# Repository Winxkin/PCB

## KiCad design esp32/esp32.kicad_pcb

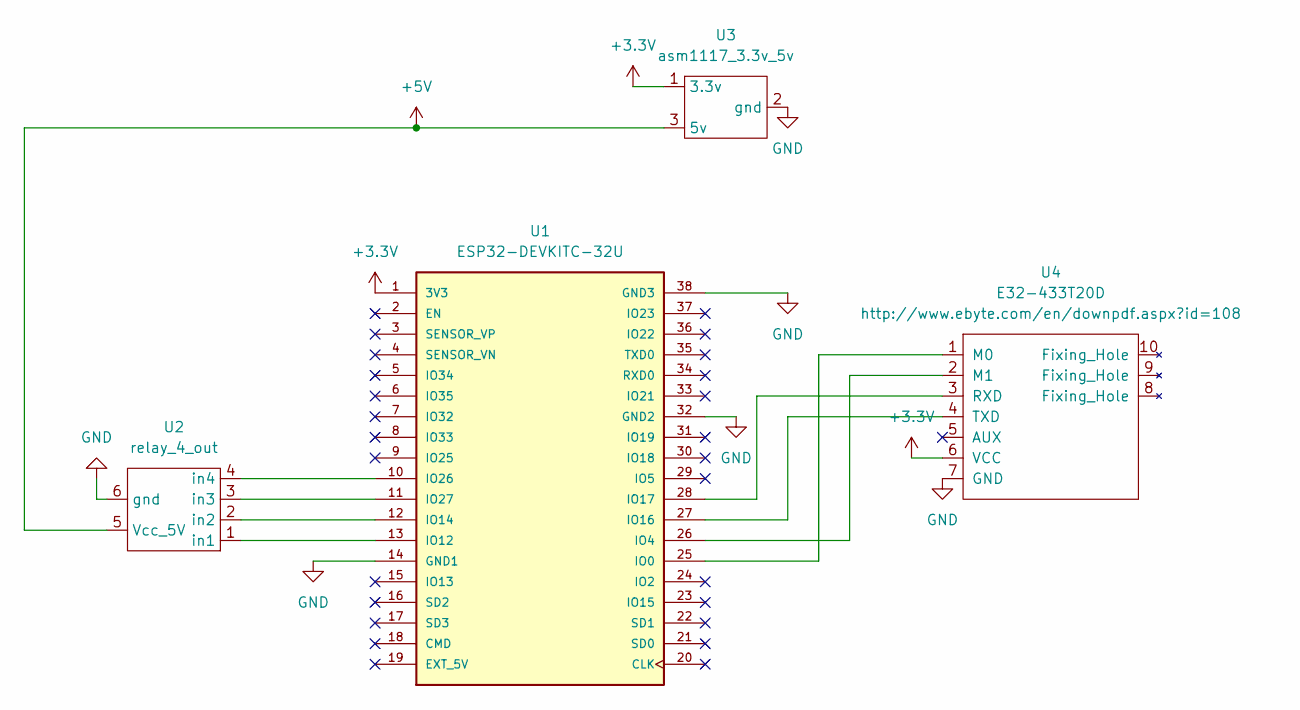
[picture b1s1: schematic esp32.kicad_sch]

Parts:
U1: ESP32-DEVKITC-32U; MODULE_ESP32-DEVKITC-AI-Thinker; PARTREV N/A
U2: relay_4_out
U3: asm1117_3.3v_5v; asm1117_3.3V_5V
U4: E32-433T20D; E32-xxxT20D

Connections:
+3.3V: U1.1 (3V3), U3.1 (3.3v), U4.6 (VCC)
+5V: U2.5 (Vcc_5V), U3.3 (5v)
GND: U1.14 (GND1), U1.32 (GND2), U1.38 (GND3), U2.6 (gnd), U3.2 (gnd), U4.7 (GND)
unnamed: U1.10 (IO26), U2.4 (in4)
unnamed: U1.11 (IO27), U2.3 (in3)
unnamed: U1.12 (IO14), U2.2 (in2)
unnamed: U1.13 (IO12), U2.1 (in1)
unnamed: U1.25 (IO0), U4.1 (M0)
unnamed: U1.26 (IO4), U4.2 (M1)
unnamed: U1.27 (IO16), U4.4 (TXD)
unnamed: U1.28 (IO17), U4.3 (RXD)

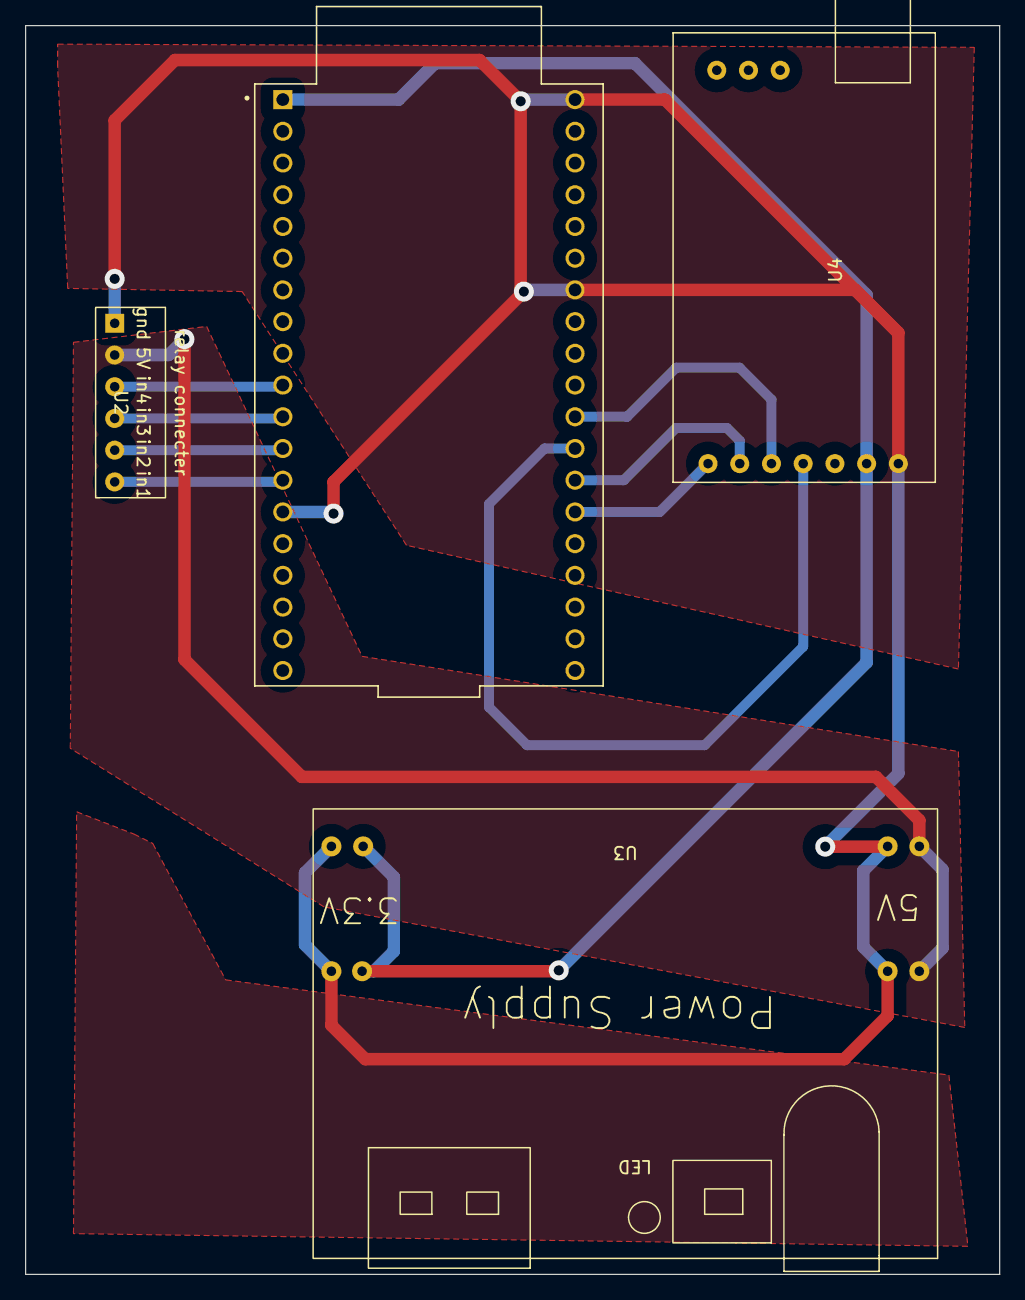
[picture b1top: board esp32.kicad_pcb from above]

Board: 2 copper layers, 78.0 x 100.0 mm, 4 parts (0 on the bottom side), 11 nets.

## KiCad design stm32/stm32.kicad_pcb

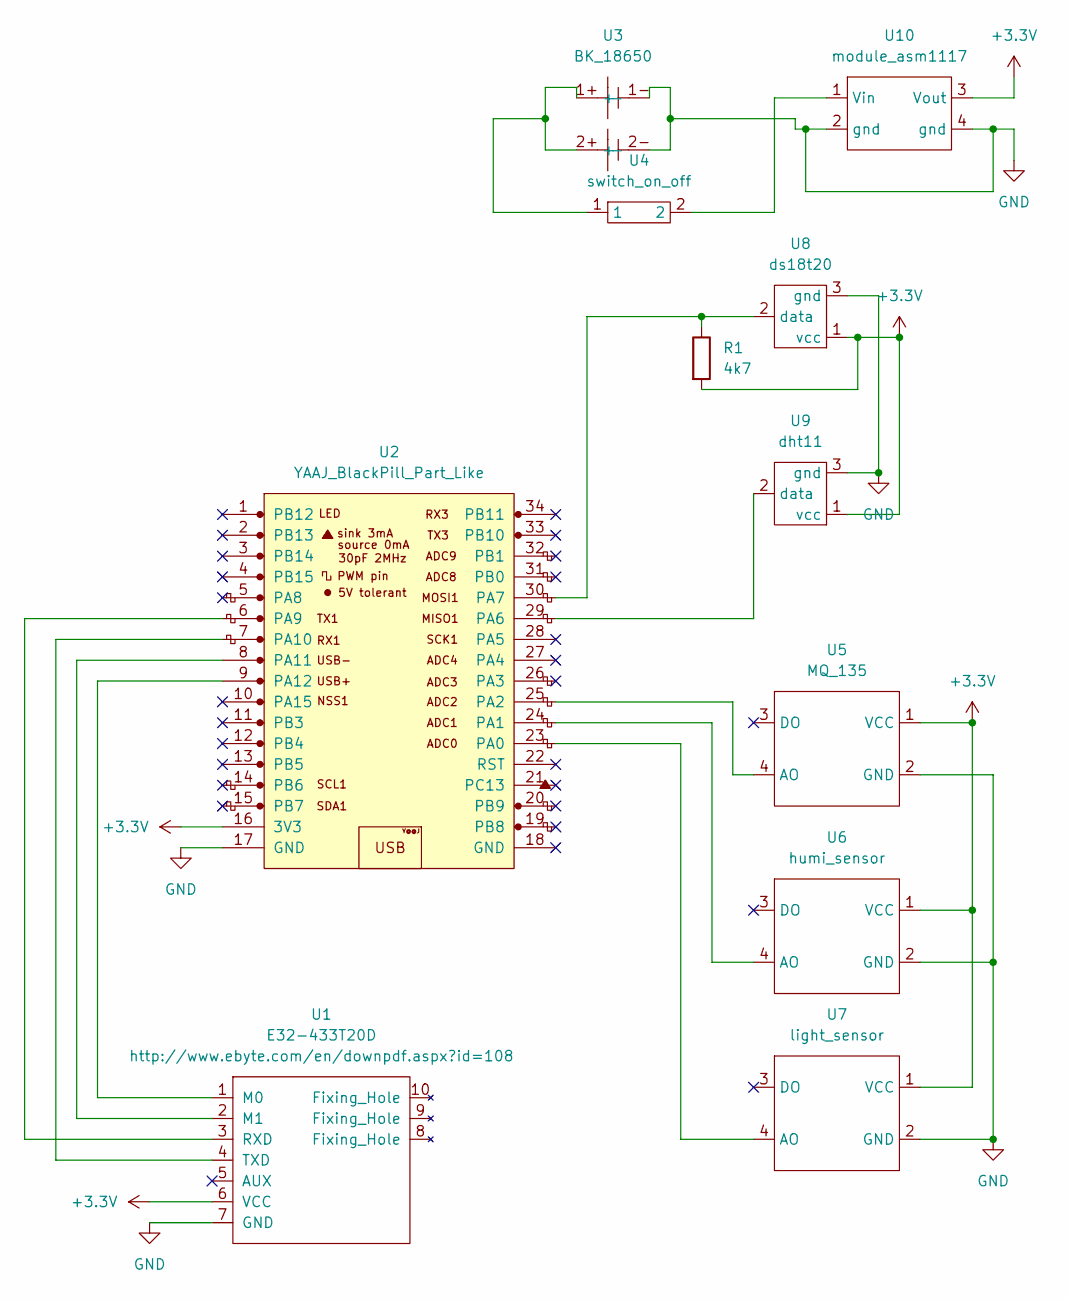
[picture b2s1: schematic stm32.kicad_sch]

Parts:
R1: 4k7; R_Axial_DIN0204_L3.6mm_D1.6mm_P2.54mm_Vertical
U1: E32-433T20D; E32-xxxT20D
U2: YAAJ_BlackPill_Part_Like; YAAJ_BlackPill_1
U3: BK_18650; BAT_BK-18650-PC4
U4: switch_on_off
U5: MQ_135
U6: humi_sensor
U7: light_sensor
U8: ds18t20; dt18s20
U9: dht11; dt18s20
U10: module_asm1117

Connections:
+3.3V: R1.2, U1.6 (VCC), U2.16 (3V3), U5.1 (VCC), U6.1 (VCC), U7.1 (VCC), U8.1 (vcc), U9.1 (vcc), U10.3 (Vout)
GND: U1.7 (GND), U2.17 (GND), U3.1- (-), U3.2- (-), U5.2 (GND), U6.2 (GND), U7.2 (GND), U8.3 (gnd), U9.3 (gnd), U10.2 (gnd), U10.4 (gnd)
unnamed: R1.1, U2.30 (PA7), U8.2 (data)
unnamed: U1.1 (M0), U2.9 (PA12)
unnamed: U1.2 (M1), U2.8 (PA11)
unnamed: U1.3 (RXD), U2.6 (PA9)
unnamed: U1.4 (TXD), U2.7 (PA10)
unnamed: U2.23 (PA0), U7.4 (AO)
unnamed: U2.24 (PA1), U6.4 (AO)
unnamed: U2.25 (PA2), U5.4 (AO)
unnamed: U2.29 (PA6), U9.2 (data)
unnamed: U3.1+ (+), U3.2+ (+), U4.1
unnamed: U4.2, U10.1 (Vin)

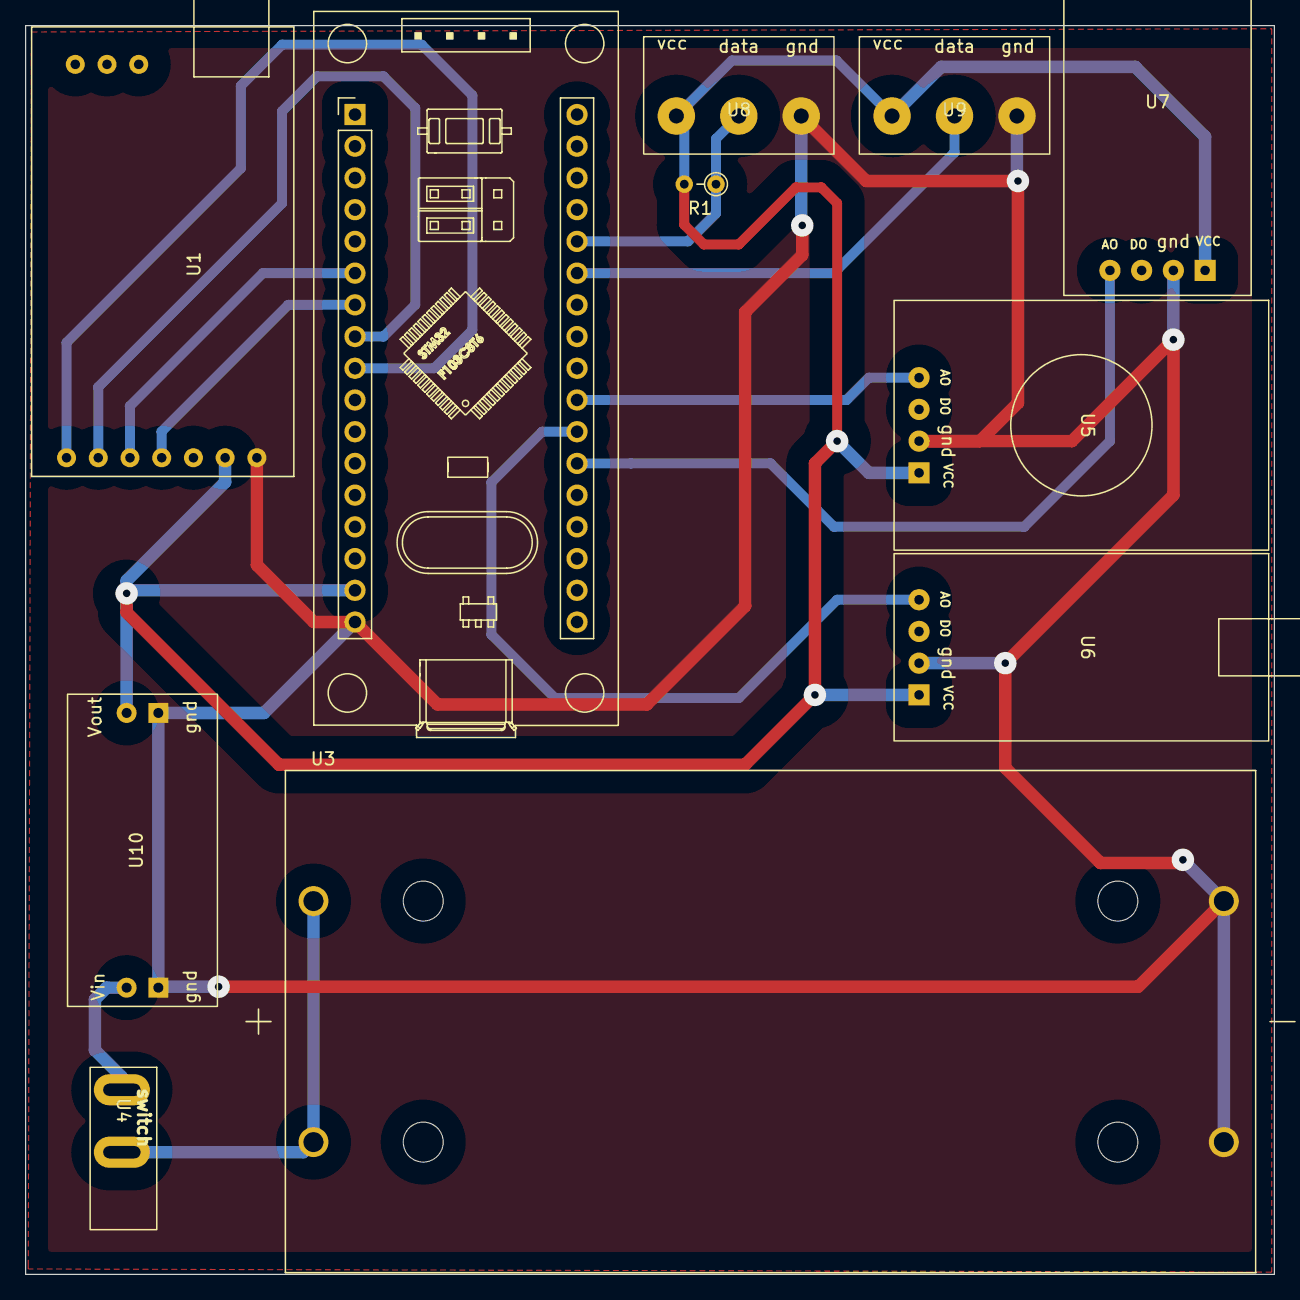
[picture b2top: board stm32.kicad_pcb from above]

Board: 2 copper layers, 100.0 x 100.0 mm, 11 parts (0 on the bottom side), 13 nets.

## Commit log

2022-10-31 add stm32
2022-11-01 esp32
